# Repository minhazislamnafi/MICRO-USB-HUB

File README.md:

# MICRO-USB-HUB

# Specification

* USB HUB
* 1 upstream & 4 downstream
* 4 USB type-C (1 upstream & 3 downstream) and 1 USB type-A
* Chip- Fe1.1s SSOP-28
* dimentions: x x (LxWxH)

# Why you will need this micro usb hub?
Beacuse you definitly need a type-C usb hub if your using a desktop computer. also as its name suggests its very small and compact measures only (50x25x16)mm. So you should build one;)

# Documentation
In this repository, you can find 3D printable STL files file the USB hub enclosure, Garber, and all the other
files to build your own 4-port compact USB HUB. 

# Quick Start

## Requirements

## Components:

* Fe1.1s ssop-28 USB hub IC x1 (https://s.click.aliexpress.com/e/_c3coFDb3)
* 16p Type-C receptical port X4 (https://s.click.aliexpress.com/e/_c3JNhMQz)
* 4p Type-A port x1 (https://s.click.aliexpress.com/e/_c4ryhZZn)
* USBLC6-2SC6 SOT-23-6 x1 (https://s.click.aliexpress.com/e/_c4aL9H4z)
* 0603 resisotr 5.1k x8 (https://s.click.aliexpress.com/e/_c3cSR54l)
* 0603 resistor 12k x1 (https://s.click.aliexpress.com/e/_c3cSR54l)
* 0603 capacitor 10uF x2 (https://s.click.aliexpress.com/e/_c42BS133)
* 0603 capacitor 22pF x2 (https://s.click.aliexpress.com/e/_c42BS133)
* 2016 Crystal oscillator x1 (https://s.click.aliexpress.com/e/_c2QYKExf)

## For detailed parts list and prices follow [BOM](BOM.csv)

# Onshape Full Assembly [LINK](https://cad.onshape.com/documents/72abdd8eb848de8d8be587be/w/fde1524f77307cafb45bef5a/e/de3ea8da0c261ec2d1304d2f?renderMode=0&uiState=6a2f2679a6140eb0eaf3c990)

## For 3D printing the enclosure 

**You will find the printable .STL file [Here](CAD/Micro%20usb%20hub.stl)**

**Slice the model in center half and print them like this.**

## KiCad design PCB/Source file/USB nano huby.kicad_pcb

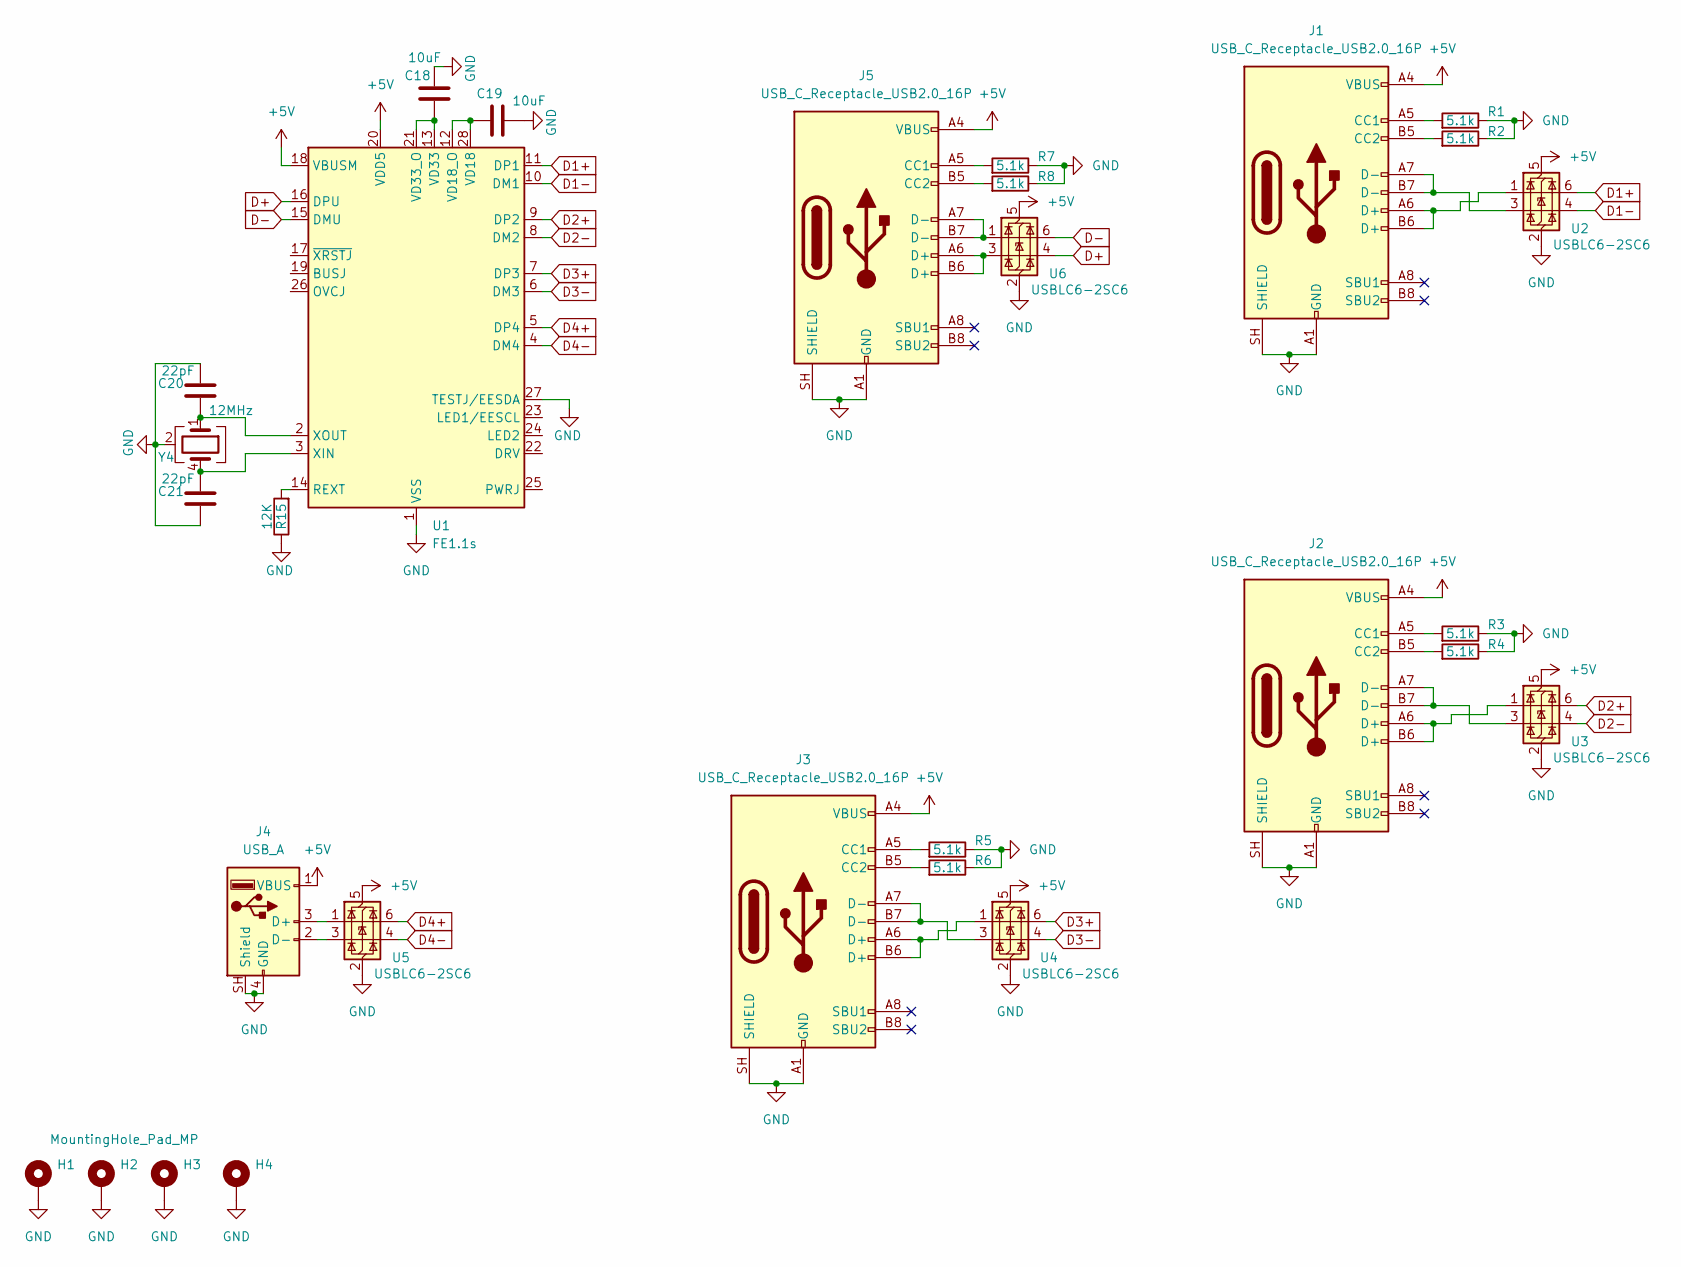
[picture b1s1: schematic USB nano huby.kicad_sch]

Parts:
C18, C19: 10uF; C_0603_1608Metric
C20, C21: 22pF; C_0603_1608Metric
H1, H2, H3, H4: MountingHole_Pad_MP; MountingHole_2.2mm_M2_DIN965_Pad
J1, J2, J3, J5: USB_C_Receptacle_USB2.0_16P; USB_C_Receptacle_GCT_USB4105-xx-A_16P_TopMnt_Horizontal
J4: USB_A; USB_A_TE_292303-7_Horizontal
R1, R2, R3, R4, R5, R6, R7, R8: 5.1k; R_0603_1608Metric
R15: 12K; R_0603_1608Metric_Pad0.98x0.95mm_HandSolder
U1: FE1.1s; SSOP-28_3.9x9.9mm_P0.635mm
U2, U3, U4, U5, U6: USBLC6-2SC6; SOT-23-6
Y4: 12MHz; Crystal_SMD_2016-4Pin_2.0x1.6mm

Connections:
+5V: J1.A4 (VBUS), J1.A9 (VBUS), J1.B4 (VBUS), J1.B9 (VBUS), J2.A4 (VBUS), J2.A9 (VBUS), J2.B4 (VBUS), J2.B9 (VBUS), J3.A4 (VBUS), J3.A9 (VBUS), J3.B4 (VBUS), J3.B9 (VBUS), J4.1 (VBUS), J5.A4 (VBUS), J5.A9 (VBUS), J5.B4 (VBUS), J5.B9 (VBUS), U1.18 (VBUSM), U1.20 (VDD5), U2.5 (VBUS), U3.5 (VBUS), U4.5 (VBUS), U5.5 (VBUS), U6.5 (VBUS)
D1+: U1.11 (DP1), U2.6 (I/O1)
D1-: U1.10 (DM1), U2.4 (I/O2)
D2+: U1.9 (DP2), U3.6 (I/O1)
D2-: U1.8 (DM2), U3.4 (I/O2)
D3+: U1.7 (DP3), U4.6 (I/O1)
D3-: U1.6 (DM3), U4.4 (I/O2)
D4+: U1.5 (DP4), U5.6 (I/O1)
D4-: U1.4 (DM4), U5.4 (I/O2)
D+: U1.16 (DPU), U6.4 (I/O2)
D-: U1.15 (DMU), U6.6 (I/O1)
GND: C18.1, C19.1, C20.1, C21.2, H1.MP, H2.MP, H3.MP, H4.MP, J1.A1 (GND), J1.A12 (GND), J1.B1 (GND), J1.B12 (GND), J1.SH (SHIELD), J2.A1 (GND), J2.A12 (GND), J2.B1 (GND), J2.B12 (GND), J2.SH (SHIELD), J3.A1 (GND), J3.A12 (GND), J3.B1 (GND), J3.B12 (GND), J3.SH (SHIELD), J4.4 (GND), J4.SH (Shield), J5.A1 (GND), J5.A12 (GND), J5.B1 (GND), J5.B12 (GND), J5.SH (SHIELD), R1.2, R2.2, R3.2, R4.2, R5.2, R6.2, R7.2, R8.2, R15.1, U1.1 (VSS), U1.27 (TESTJ/EESDA), U2.2 (GND), U3.2 (GND), U4.2 (GND), U5.2 (GND), U6.2 (GND), Y4.2 (G), Y4.3 (G)
unnamed: J1.A5 (CC1), R1.1
unnamed: J1.B5 (CC2), R2.1
unnamed: J1.A6 (D+), J1.B6 (D+), U2.1 (I/O1)
unnamed: J1.A7 (D-), J1.B7 (D-), U2.3 (I/O2)
unnamed: J2.A5 (CC1), R3.1
unnamed: J2.B5 (CC2), R4.1
unnamed: J2.A6 (D+), J2.B6 (D+), U3.1 (I/O1)
unnamed: J2.A7 (D-), J2.B7 (D-), U3.3 (I/O2)
unnamed: J3.A5 (CC1), R5.1
unnamed: J3.B5 (CC2), R6.1
unnamed: J3.A6 (D+), J3.B6 (D+), U4.1 (I/O1)
unnamed: J3.A7 (D-), J3.B7 (D-), U4.3 (I/O2)
unnamed: J4.3 (D+), U5.1 (I/O1)
unnamed: J4.2 (D-), U5.3 (I/O2)
unnamed: J5.A5 (CC1), R7.1
unnamed: J5.B5 (CC2), R8.1
unnamed: J5.A6 (D+), J5.B6 (D+), U6.3 (I/O2)
unnamed: J5.A7 (D-), J5.B7 (D-), U6.1 (I/O1)
unnamed: R15.2, U1.14 (REXT)
unnamed: C19.2, U1.12 (VD18_O), U1.28 (VD18)
unnamed: C18.2, U1.13 (VD33), U1.21 (VD33_O)
unnamed: C21.1, U1.3 (XIN), Y4.4
unnamed: C20.2, U1.2 (XOUT), Y4.1

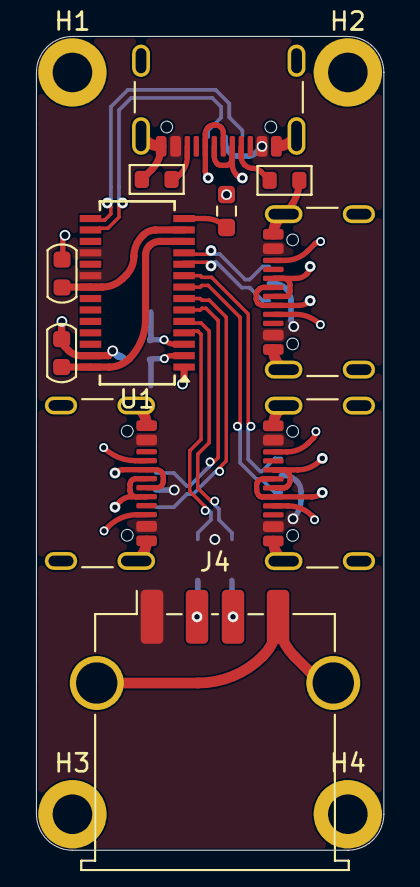
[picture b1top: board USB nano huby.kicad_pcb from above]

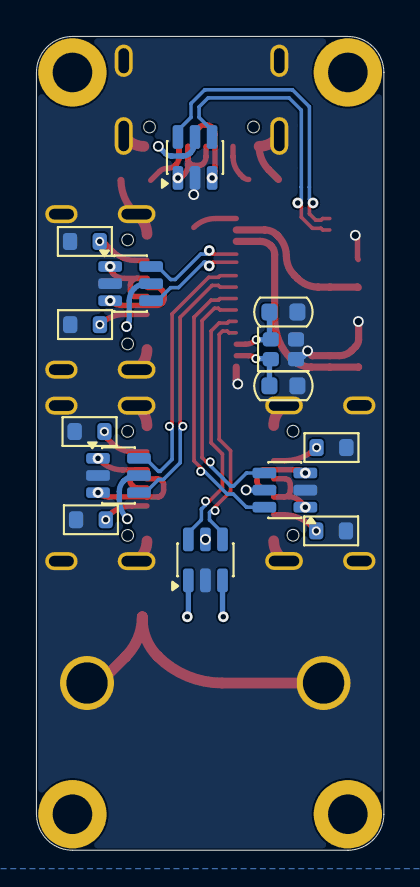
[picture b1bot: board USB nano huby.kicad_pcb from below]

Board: 2 copper layers, 19.3 x 45.2 mm, 29 parts (14 on the bottom side), 35 nets.

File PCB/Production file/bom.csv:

Designator,Footprint,Quantity,Value,LCSC Part #
"C18, C19",0603,2,10uF,
"C20, C21",0603,2,22pF,
"J1, J2, J3, J5",USB_C_Receptacle_GCT_USB4105-xx-A_16P_TopMnt_Horizontal,4,USB_C_Receptacle_USB2.0_16P,
J4,USB_A_TE_292303-7_Horizontal,1,USB_A,
"R1, R2, R3, R4, R5, R6, R7, R8",0603,8,5.1k,
R15,0603,1,12K,
U1,SSOP-28_3.9x9.9mm_P0.635mm,1,FE1.1s,
"U2, U3, U4, U5, U6",SOT-23-6,5,USBLC6-2SC6,
Y4,Crystal_SMD_2016-4Pin_2.0x1.6mm,1,12MHz,

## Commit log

2026-06-14 Replace MIT License with CERN Open Hardware Licence
2026-06-14 Create 1
2026-06-14 Rename USB nano huby.pdf to USB nano huby_sch.pdf
2026-06-14 Rename USB_nano_huby.zip to USB_nano_huby_GARBER.zip
2026-06-15 Rename Zine (2).pdf to Zine.pdf
2026-06-17 Rename Micro USB HUB.pdf to Zine.pdf
2026-06-17 Fix typos and update total price in BOM.csv
2026-06-17 Update parts list in README with new components
    Added additional components to the parts list in the README.
2026-06-17 Update README with 3D printing instructions and links
    Added section for 3D printing the enclosure and updated links.

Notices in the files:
README.md:
License: OHL v2
